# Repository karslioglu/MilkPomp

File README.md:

# Milk Pomp
Proje, kullanicinin farkli tip ve hacimli bardaklara makineden süt doldurmak için kullanilacak bir cihazin kontrol kartinin tasarlanmasi işidir.

Cihazın mekanik tasarımı, flow sensör ve pompa seçimi müşteri tarafından hazırlanmıştır. Bizim yapacağımız iş ise sistemin çalışmasını sağlayacak elektronik kontrol kartının tasarlanmasıdır.

## Sistemin Çalismasi
Cihaz maksimum 9 farklı bardak bilgisini hafızada tutabilir. Kullanıcı bardak seçimi yaparak kayıtlı bardak tiplerinden birini otomatik olarak doldurabilir. Fakat istenirse kayıtlı olmayan farklı bir kabı da manuel olarak istediği miktarda doldurabilir.

Cihaz üzerinde 3 adet buton ve 1 adet 7-Segment gösterge bulunmaktadır. Ayrıca, bir pulse girişi ile **Akış Sensoru** girişi okunacak ve çıkış olarak bir role kontrol edilecektir.

	* I/O (On/Off) butonu
	* Start butonu
	* Mode butonu
	* Akış Sensoru (Encoder Pulse Input)
	* Role

Aşağıda tarif edilen çalışma şekilleri bu 3 buton ve gösterge kullanılarak gerçeklenecektir.

Sistemi çalıştırmak için I/O butonuna bir kere basıp bırakmak yeterlidir. Sistem kapalıyken gösterge ve diğer butonlar aktif değildir. I/O butonuna bir kere basılıp bırakıldığında sistem açılır, eğer kalibrasyon yapılmamışsa (hiç bardak tanımı yoksa) **C.** değeri görünür ve ekran yanıp söner. Aksi halde sabit olarak **0** yazar ve bardak seçimi için bekler.

Cihaz 3 farklı çalışma şekline sahip olacaktır.

### Kalibrasyon
Kalibrasyon modu, elimizde bulunan bardakların tanımlanması için kullanılır. Maksimum 9 farklı bardak tanımı yapılabilir.

Kalibrasyon modu bir adet bardak tanıtmak istenirse aşağıdaki algoritmaya göre çalışır

	1- Kalibrasyonu başlatmak için I/O butonuna 5 saniye basılı tutulur
	2- Gösterge 0 değerini gösterir ve nokta yanıp sönmeye başlar
	3- İstenilen bardak, cihazın bardak bölmesine yerleştirilir
	4- Mode butonu ile bardak seçimi yapılır (1, 2, 3, ..)
	5- Start butonuna basılı tutularak bardak doldurulur
	6- Bardak dolunca Start butonu bırakılır
	7- Start butonu bırakıldığında seçilen bardak ve doldurulan miktar bilgileri otomatik olarak kaydedilir
	8- Kalibrasyon modundan çıkmak için I/O butonuna 5 saniye bayunca basılır
	
Eğer birden fazla bardak tanımı yapılmak istenirse yukarıdaki algoritma basamaklarından 1 nolu adım ile kalibrasyon işlemi başlatılır. 2-7 adımları her bir bardak için tekrarlanır. Tüm bardakların tanımlanma işlemi bittiğinde 8 nolu adım ile kalibrasyon işlemi sonlandırılır.

Daha sonra tanımlı bir bardağın kalibrasyonu değiştirlmek istendiğinde veya yeni bir bardak tanımı yapılması gerektiğinde yukarıdaki algoritma tekrar uygulanabilir.

> Dikkat edilmesi gereken nokta, eğer bardak tanımları yapılmış bir cihazda tek bir bardağın kalibrasyonu değiştirlmek istenirse, Mode butonu ile doğru bardak numarasının seçildiğinden emin olunması gerekmektedir.

### Otomatik Mod
Kalibrasyonu yapılmış bir cihazda kullanıcı bardak seçimi yaparak tanımlı bardaklardan birini otomatik olarak doldurabilir.

	1- İstenilen bardak, cihazın bardak bölmesine yerleştirilir
	2- Mode butonu kullanılarak bardak seçimi yapılır
	3- Start butonuna basılıp bırakıldığında tanımlı miktar kadar dolum yapılır
	
Her bir bardak için yukarıdaki adımlar tekrarlanır.

### Manuel Mod
Kalibrasyon yapılarak tanımlanmamış bir bardak veya farklı bir kap doldurulmak istendiğinde Manuel mod kullanılır.

	1- Doldurulmak istenilen kap yerleştirilir.
	2- Start butonuna basılı tutulur. Butona basıldıktan 5 saniye sonra manuel dolum başlar
	3- Kullanıcı Start butonunu bıraktığında dolum işlemi sonlanır.

## Kullanilacak Bilesenler
[flow sensor](https://www.hepsiburada.com/fluidotech-kahve-makinasi-pompasi-rotary-pompa-pirinc-govdeli-p-HBV000007SB1Q)
[flow sensor kullanimi](https://how2electronics.com/iot-water-flow-meter-using-esp8266-water-flow-sensor/)

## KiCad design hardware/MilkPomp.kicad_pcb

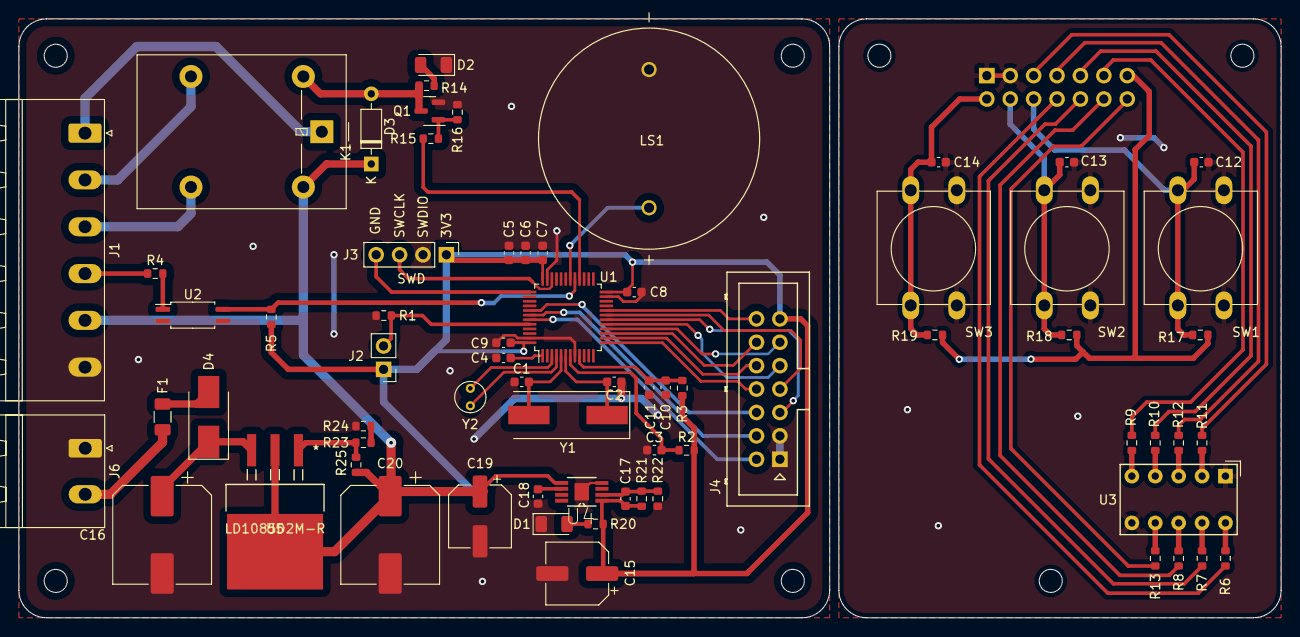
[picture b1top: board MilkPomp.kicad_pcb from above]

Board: 2 copper layers, 137.0 x 65.0 mm, 76 parts (1 on the bottom side), 62 nets.

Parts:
C1, C2: 20pF; C_0603_1608Metric
C3, C5, C7, C8, C9, C10, C12, C13, C14: 100nF; C_0603_1608Metric
C4: 1uF/10V; C_0603_1608Metric
C6, C11: 1uF/6V; C_0603_1608Metric
C15: 10uF/10V; CP_Elec_6.3x7.7
C16, C20: 100uF/35V; CP_Elec_10x10.5
C17, C18: 10nF; C_0603_1608Metric
C19: 10uF/35V; CP_Elec_6.3x7.7
D1, D2: LED_GREEN; LED_1206_3216Metric
D3: 1N4148; D_DO-35_SOD27_P7.62mm_Horizontal
D4: SBR3A40SAQ; D_SMB_Handsoldering
F1: 1A; Fuse_1206_3216Metric
H1, H2, H3, H4, H5, H6, H7: MountingHole; MountingHole_2.5mm
J1: Screw_Terminal_01x06; PhoenixContact_MSTBA_2,5_6-G-5,08_1x06_P5.08mm_Horizontal
J2: BOOT; PinHeader_1x02_P2.54mm_Vertical
J3: Conn_01x04_Male; PinHeader_1x04_P2.54mm_Vertical
J4: Conn_Board; Multicomp_MC9A12-1434_2x07x2.54mm_Straight
J5: Conn_Display; Multicomp_MC9A12-1434_2x07x2.54mm_Straight
J6: PWR INPUT; PhoenixContact_MSTBA_2,5_2-G_1x02_P5.00mm_Horizontal
K1: G5LE-1; Relay_SPDT_Omron-G5LE-1
LS1: KPEG228; XDCR_KPEG228
Q1: BC847; SOT-23
R1, R2: 100K; R_0603_1608Metric
R3: 100R; R_0603_1608Metric
R4: 3K3; R_0603_1608Metric
R5, R14, R15: 4K7; R_0603_1608Metric
R6, R7, R8, R9, R10, R11, R12, R13: 330R; R_0603_1608Metric
R16: 47K; R_0603_1608Metric
R17, R18, R19, R22: 10K; R_0603_1608Metric
R20: 470; R_0603_1608Metric
R21: 18K; R_0603_1608Metric
R23: 1K; R_0603_1608Metric
R24: 33; R_0603_1608Metric
R25: 120; R_0603_1608Metric
SW1: SW_IO; SW_PUSH-12mm
SW2: SW_START; SW_PUSH-12mm
SW3: SW_MODE; SW_PUSH-12mm
U1: STM32F103C8Tx; LQFP-48_7x7mm_P0.5mm
U2: TLP291; SOIC-4_4.55x2.6mm_P1.27mm
U3: HDSP-7403; HDSP-7401
U4: TPS7A4901DGNT; SOP65P490X110-9N
U5: LD1085D2M-R
Y1: 8MHz; Crystal_SMD_HC49-SD
Y2: 32KHz; Crystal_C38-LF_D3.0mm_L8.0mm_Vertical

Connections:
+3V3: C5.1, C6.1, C7.1, C8.1, C9.1, C15.1, C17.1, J2.1, J3.1, J4.13, J5.13, R2.2, R3.1, R5.1, R17.1, R18.1, R19.1, R20.1, R21.1, U1.24 (VDD), U1.36 (VDD), U1.48 (VDD), U4.1 (OUT)
+12V: C19.1, C20.1, D3.1 (K), J1.5, K1.5, R25.1, U4.5 (EN), U4.8 (IN), U5.2 (OUTPUT), U5.4 (OUTPUT)
/Buttons/BTN_IO: C12.1, J5.6, R17.2, SW1.2
/Buttons/BTN_MODE: C14.1, J5.2, R19.2, SW3.2
/Buttons/BTN_START: C13.1, J5.4, R18.2, SW2.2
/DISPLAY/DISP_A: J5.8, R6.1
/DISPLAY/DISP_B: J5.10, R7.1
/DISPLAY/DISP_C: J5.12, R8.1
/DISPLAY/DISP_D: J5.11, R9.1
/DISPLAY/DISP_E: J5.9, R10.1
/DISPLAY/DISP_F: J5.5, R11.1
/DISPLAY/DISP_G: J5.7, R12.1
/DISPLAY/DISP_P: J5.14, R13.1
/Flow/FLOW_SENSOR: J1.4, R4.1
/Power/LED_PWR: D1.2 (A), R20.2
/Power/VCC: F1.2, J6.2
/Relay/RELAY_IN: J1.1, K1.1
/Relay/RELAY_NC: J1.3, K1.4
/Relay/RELAY_NO: J1.2, K1.3
BOOT0: J2.2, R1.1, U1.44 (BOOT0)
BTN_IO: J4.6, U1.41 (PB5)
BTN_MODE: J4.2, U1.43 (PB7)
BTN_START: J4.4, U1.42 (PB6)
BUZZER: LS1.P, U1.30 (PA9)
DISP_A: J4.8, U1.13 (PA3)
DISP_B: J4.10, U1.14 (PA4)
DISP_C: J4.12, U1.15 (PA5)
DISP_D: J4.11, U1.16 (PA6)
DISP_E: J4.9, U1.17 (PA7)
DISP_F: J4.5, U1.18 (PB0)
DISP_G: J4.7, U1.19 (PB1)
DISP_P: J4.14, U1.20 (PB2)
FLOW: R5.2, U1.29 (PA8), U2.4
GND: C1.1, C2.1, C3.2, C4.2, C5.2, C6.2, C7.2, C8.2, C9.2, C10.2, C11.2, C12.2, C13.2, C14.2, C15.2, C16.2, C18.2, C19.2, C20.2, D1.1 (K), D2.1 (K), J1.6, J3.2, J4.1, J4.3, J5.1, J5.3, J6.1, LS1.N, Q1.2 (E), R1.2, R16.2, R22.2, R24.2, SW1.1, SW2.1, SW3.1, U1.8 (VSSA), U1.23 (VSS), U1.35 (VSS), U1.47 (VSS), U2.2, U2.3, U3.1 (CC), U3.6 (CC), U4.4 (GND), U4.9 (THERMAL_PAD)
unnamed: C4.1, U1.1 (VBAT)
unnamed: C10.1, C11.1, R3.2, U1.9 (VDDA)
unnamed: C16.1, D4.1 (K), U5.3 (INPUTS)
unnamed: C17.2, R21.2, R22.1, U4.2 (FB)
unnamed: C18.1, U4.6 (NR/SS)
unnamed: D2.2 (A), R14.1
unnamed: D3.2 (A), K1.2, Q1.3 (C), R14.2
unnamed: D4.2 (A), F1.1
unnamed: Q1.1 (B), R15.2, R16.1
unnamed: R4.2, U2.1
unnamed: R6.2, U3.10 (A)
unnamed: R7.2, U3.9 (B)
unnamed: R8.2, U3.8 (C)
unnamed: R9.2, U3.5 (D)
unnamed: R10.2, U3.4 (E)
unnamed: R11.2, U3.2 (F)
unnamed: R12.2, U3.3 (G)
unnamed: R13.2, U3.7 (DP)
unnamed: R23.1, R25.2, U5.1 (ADJ)
unnamed: R23.2, R24.1
RCC_OSC32_IN: U1.3 (PC14), Y2.2
RCC_OSC32_OUT: U1.4 (PC15), Y2.1
RCC_OSC_IN: C1.2, U1.5 (PD0), Y1.2
RCC_OSC_OUT: C2.2, U1.6 (PD1), Y1.1
RELAY: R15.1, U1.28 (PB15)
SWCLK: J3.4, U1.37 (PA14)
SWDIO: J3.3, U1.34 (PA13)
nRESET: C3.1, R2.1, U1.7 (NRST)

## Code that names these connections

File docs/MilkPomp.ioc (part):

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Mcu.Name=STM32F103C(8-B)Tx
Mcu.Package=LQFP48
Mcu.UserName=STM32F103C8Tx
PA13.Mode=Serial_Wire
PA13.Signal=SYS_JTMS-SWDIO
PA14.Mode=Serial_Wire
PA14.Signal=SYS_JTCK-SWCLK
PA3.GPIOParameters=GPIO_Label
PA3.GPIO_Label=DISP_A
PA3.Signal=GPIO_Output
PA4.GPIOParameters=GPIO_Label
PA4.GPIO_Label=DISP_B
PA4.Signal=GPIO_Output
PA5.GPIOParameters=GPIO_Label
PA5.GPIO_Label=DISP_C
PA5.Signal=GPIO_Output
PA6.GPIOParameters=GPIO_Label
PA6.GPIO_Label=DISP_D
PA6.Signal=GPIO_Output
PA7.GPIOParameters=GPIO_Label
PA7.GPIO_Label=DISP_E
PA7.Signal=GPIO_Output
PA8.GPIOParameters=GPIO_Label
PA8.GPIO_Label=FLOW
PA8.Signal=S_TIM1_CH1
PA9.GPIOParameters=GPIO_Label
PA9.GPIO_Label=BUZZER
PA9.Signal=S_TIM1_CH2
PB0.GPIOParameters=GPIO_Label
PB0.GPIO_Label=DISP_F
PB0.Signal=GPIO_Output
PB1.GPIOParameters=GPIO_Label
PB1.GPIO_Label=DISP_G
PB1.Signal=GPIO_Output
PB15.GPIOParameters=GPIO_Label
PB15.GPIO_Label=RELAY
PB15.Signal=GPIO_Output
PB2.GPIOParameters=GPIO_Label
PB2.GPIO_Label=DISP_P
PB2.Signal=GPIO_Output
PB5.GPIOParameters=GPIO_Label
PB5.GPIO_Label=BTN_IO
PB5.Signal=GPXTI5
PB6.GPIOParameters=GPIO_Label
PB6.GPIO_Label=BTN_START
PB6.Signal=GPXTI6
PB7.GPIOParameters=GPIO_Label
PB7.GPIO_Label=BTN_MODE
PB7.Signal=GPXTI7
PC14-OSC32_IN.Mode=LSE-External-Oscillator
PC14-OSC32_IN.Signal=RCC_OSC32_IN
PC15-OSC32_OUT.Mode=LSE-External-Oscillator
PC15-OSC32_OUT.Signal=RCC_OSC32_OUT
PD0-OSC_IN.Mode=HSE-External-Oscillator
PD0-OSC_IN.Signal=RCC_OSC_IN
PD1-OSC_OUT.Mode=HSE-External-Oscillator
PD1-OSC_OUT.Signal=RCC_OSC_OUT
RCC.HSEDivPLL=RCC_HSE_PREDIV_DIV2
RCC.HSE_VALUE=16000000
RCC.SYSCLKFreq_VALUE=72000000
RCC.SYSCLKSource=RCC_SYSCLKSOURCE_PLLCLK
board=custom

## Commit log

2022-11-01 Init repo
2022-11-01 Sistemin calismasi aciklandi
2022-11-01 README fixed
2022-11-02 gitignore file added to root path
2022-11-07 Main page and MCU pace created
2022-11-21 Input buttons changed
2022-11-21 MCU module is completed
2022-11-21 MCU SW fixed
2022-11-21 değişiklik yapıldı
2022-11-21 Block Diagram changed
2022-11-21 Buttons module completed by Utku CAM
2022-11-21 Relay module completed
2022-11-21 .Ds_Store ignored
2022-11-21 Display circuit added
2022-11-22 flow sensor Flow sensor added to readme file
2022-11-22 ESP8266 with Water Flow Sensor added
2022-11-22 Flow module completed
2022-11-24 Schematics are completed
2022-11-25 milkpomp pcb continued
2022-11-29 PCB designed
2022-11-30 PCB designed2
2022-11-30 Footprints are assigned and Cut edges fixed
2022-11-30 PCB drawing completed
2022-12-01 All PCB drawing completed
2022-12-01 PCB design completed
2022-12-02 All PCB design completed
2023-07-14 yeni seyler eklendi

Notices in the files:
parts and their libraries:
Copyright 2016 Accelerated Designs. All rights reserved.
